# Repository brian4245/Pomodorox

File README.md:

# Pomodorox
Pomodorox is a project that helps to the high school´s students for studying without distractions

On shape: https://cad.onshape.com/documents/2d539401d5eeff7b5a051a5e/w/acb2298a33fe291c39ed5225/e/8e80be298c9f318b740c5d51?renderMode=0&uiState=6a6d26c64163ef4042c04433

# Motivation
Well, I did this project because I realized that many people try to study but many times they don´t study, and it is because we use a laptop or a smarthphone to use a technique for study, but many times these technology products give us many distractions, and the better option to use could be an analogyc product that you can use to study.

# Instructions to build it
After all I know you the functions that I used for the circuit, I used the default functions like setup and loop. In adittion I use these functions:
void ultrasonico(); this function is to start the work of ultrasonic distance sensor, it starts when you press the red button in the IR remote, and it detects if you are near or far, and if you near the circuit start to works as a pomodoro.
``` C++
void reset(); //This one is to reset the values of time at the pomodoro (twenty five minutes).
void reloj(); //This another one is to start the clock pomodoro for study time.
void descanso(); //This one is to start the break (five minutes).
void start(); //This one is to start the words that going to give you a gretting.
void plazos(); // With this one you can decides if you wanna continue with the break or with the focus time.
```

Well, first you need to configure you ultrasonic distance sensor for detects the distance in a well way. I this step I use this code to configure it: 
``` C++
void ultrasonico(){ 
  digitalWrite(trigpin, LOW);  
  delayMicroseconds(2);
  digitalWrite(trigpin, HIGH);
  delayMicroseconds(10); 
  digitalWrite(trigpin, LOW);
  
  duration = pulseIn(echopin, HIGH);
  distance = duration / 58.2;
  Serial.println(distance);
}
```
I use a function to become the code more versatil. Oh, before it you need to place the pins at setup, like this:
```C++
pinMode(trigpin, OUTPUT);
pinMode(echopin, INPUT);
```
Variables:
```C++
int trigpin = 4;
int echopin = 5;
```
Well after it, now you need to configure the IR remote and the IR sensor to POMODORO going to able to detect you position in yout desktop and If you really study. For it, I use this variable:
```C++
int IRD = 3;
```
Then I placed it at setup to begin the IR sensor:
```C++
  IrReceiver.begin(IRD);
```
Well, after it the third step is to configure the button that you use to start the system of POMODORO, I placed the code in loop:
```C++
 int IRcode = 0; 
  if(IrReceiver.decode()){
    IRcode = IrReceiver.decodedIRData.command; 
    Serial.println(IRcode);
    IrReceiver.resume();
  }
```
Well I declared " int IRcode = 0 " to avoid some mistkae with the control at the moment I don´t need it more, and I place the conditional to start the IR sensor for the code, IRcode is the Data number that the IRremote give us, Then I print it in monitor serial, after it I reset the IRcode, to start all again.
```C++
 if (IRcode == 162){
    startcontrol = true; <= this function is to start the greeting at the display
    ultrasonicocontrol = true; <= this one is to start the ultrasonic distance to POMODORO can see if you are near (1m).
    yasepuede = true; <= this one is for the POMODORO can understand that you are ready.
  }
```
Well, after it you need to configure the code for the chronometer, this step is very crucial because you need it to do working the POMODORO

Well, this code I used for the chronometer in the focus time.
```C++
void reloj(){
  lcd.setCursor(0, 0);
  lcd.print("POMODORO");
  lcd.setCursor(0, 1);
  
  if (MINUTOS < 10) lcd.print("0"); 
  lcd.print(MINUTOS);
  lcd.print(":");
  if (SEGUNDOS < 10) lcd.print("0"); 
  lcd.print(SEGUNDOS);
  
  cronometrofocus = true;
}
```
 Within that code I placed the boolean variable "cronometrofocus" it is in charge to do works the chronometer in reality.
```C++
  // 5. CRONÓMETROS 
  if (cronometrofocus == true){
    if (millis() - tiempoinicio >= 1000){
      tiempoinicio = millis();
      SEGUNDOS++;
      if (SEGUNDOS == 60){
        SEGUNDOS = 0;
        MINUTOS++;
      }
    }
  }
  
  if (cronometrodespeje == true){
    if (millis() - tiempoiniciodescanso >= 1000){
      tiempoiniciodescanso = millis();
      SEGUNDOSD++;
      if (SEGUNDOSD == 60){
        SEGUNDOSD = 0;
        MINUTOSD++;
      }
    }
  }
```
Well at that code chronometer that I use, because they have a similar system to work the only thing that changes is the variables.
Well and the function for the break works in a similar way like the function for the focus time.
```C++
void descanso(){
  lcd.setCursor(9, 0);
  lcd.print("DESCANSO");
  lcd.setCursor(9, 1);
  if (MINUTOSD < 10) lcd.print("0"); 
  lcd.print(MINUTOSD);
  lcd.print(":");
  if (SEGUNDOSD < 10) lcd.print("0"); 
  lcd.print(SEGUNDOSD);
  
  cronometrodespeje = true;
}

```
The only thing that change is the place where the message is locate.

Well, the another function works when you press the red button:
```C++
void start(){
  yasepuede = true;
  ultrasonico(); // Ejecutamos la lectura real del sensor antes de evaluar
  if (distance <= 100 && distance > 0){ 
    digitalWrite(bocina, HIGH);
    lcd.setCursor(0,0);
    lcd.print("EMPEZEMOS");
    delay(1000);
    lcd.clear();
    lcd.print("LET'S MOVE ON");
    delay(1000);
    lcd.clear();
    digitalWrite(bocina, LOW);
  }
}
```
I placed the boolean variable to controle the if the clock is able to works or maybe no.

Then in the same place I placed the control for the distance, it controls if you are near or far to the POMODORO. Well I named the LED as "bocina". because at first I was thinking use an Piezo, but after thinking well I realized that is better use a LED, because it is less anoying. 

Well, I use some boolean variables to control the functions in a better way:
```C++
  if (startcontrol == true){
    start();
    startcontrol = false;
  }
  
  if (RELOJ == true){
    reloj();
  } 

  if (descansocontrol == true){
    descanso();
  }
```
I placed it at loop.

Well, I used this code to control the buttons, it was more useful because it avoid that the code confuse with another delay, because at first I used delay, but it didn´t work in a well way, so is better to use millis to control a multitasking.
```C++
  ActualFocus = digitalRead(focus);
  if (ActualFocus == HIGH && AnteriorFocus == LOW && yasepuede == true) {
    reset(); // Reseteamos los tiempos justo al empezar el tramo
    RELOJ = true;
    descansocontrol = false;
    cronometrodespeje = false;
    delay(50); // Pa que no se repita
  }
  AnteriorFocus = ActualFocus;

  ActualDespeje = digitalRead(despeje);
  if (ActualDespeje == HIGH && AnteriorDespeje == LOW && yasepuede == true) {
    reset(); 
    controlplazos = false;
    descansocontrol = true;
    RELOJ = false;
    cronometrofocus = false;
    delay(50); // Pa que no se repita
  }
  AnteriorDespeje = ActualDespeje;
```

### ¿How I use it?
It´s very easy to use, the only thing that you do is press the red button in the IR remote control when you are near (1m) to pomodorox. After it, the scren give you some instructions to continue the pomodoro (the button green is for continue studying and the other button green is for the break).
## Materials ##
- 1 Arduino uno
- 1 resistor
- 1 led
- 2 push buttons 
- 1 Ultrasonic distance sensor
-  1 IR sensor
-  1 IR remote

## Schematic ##

## BOM ##
| ITEM | Purpose | Price | Source |
| :---: | :---: | :---: | :---: |
| Ultrasonic Distance Sensor | Detect the distance where you are, and it decides if you are ready to study | S/ 8|  Nanoparuro |
| LED(red) | It is a signal to know if the Ultrasonic sensor is on | S/ 1.00 | Nanoparuro |
| Arduino UNO | It is to control the circuit | S/ 30.00 | Nanoparuro  |
| I2C LCD | It is to use with fewer pins | S/ 7.00 | Nanoparuro  |
| LCD 20x4 | It is crucial to represent the chronometer POMODORO | S/ 22.00 | Electromanía  |
| IR remote | It is for controlling the start of the pomodoro | S/ 10.00 | Nanoparuro |
| IR sensor | It is to detect the IR remote | S/ 10.00 | Nanoparuro  |
| 2 Push Buttons | To activate the POMODORO clock | S/ 1.40 | electromanía |
| PCB | To conncect all of the componentes in the circuit | S/ 120 | VILLACONTROL |

## Magazine ##

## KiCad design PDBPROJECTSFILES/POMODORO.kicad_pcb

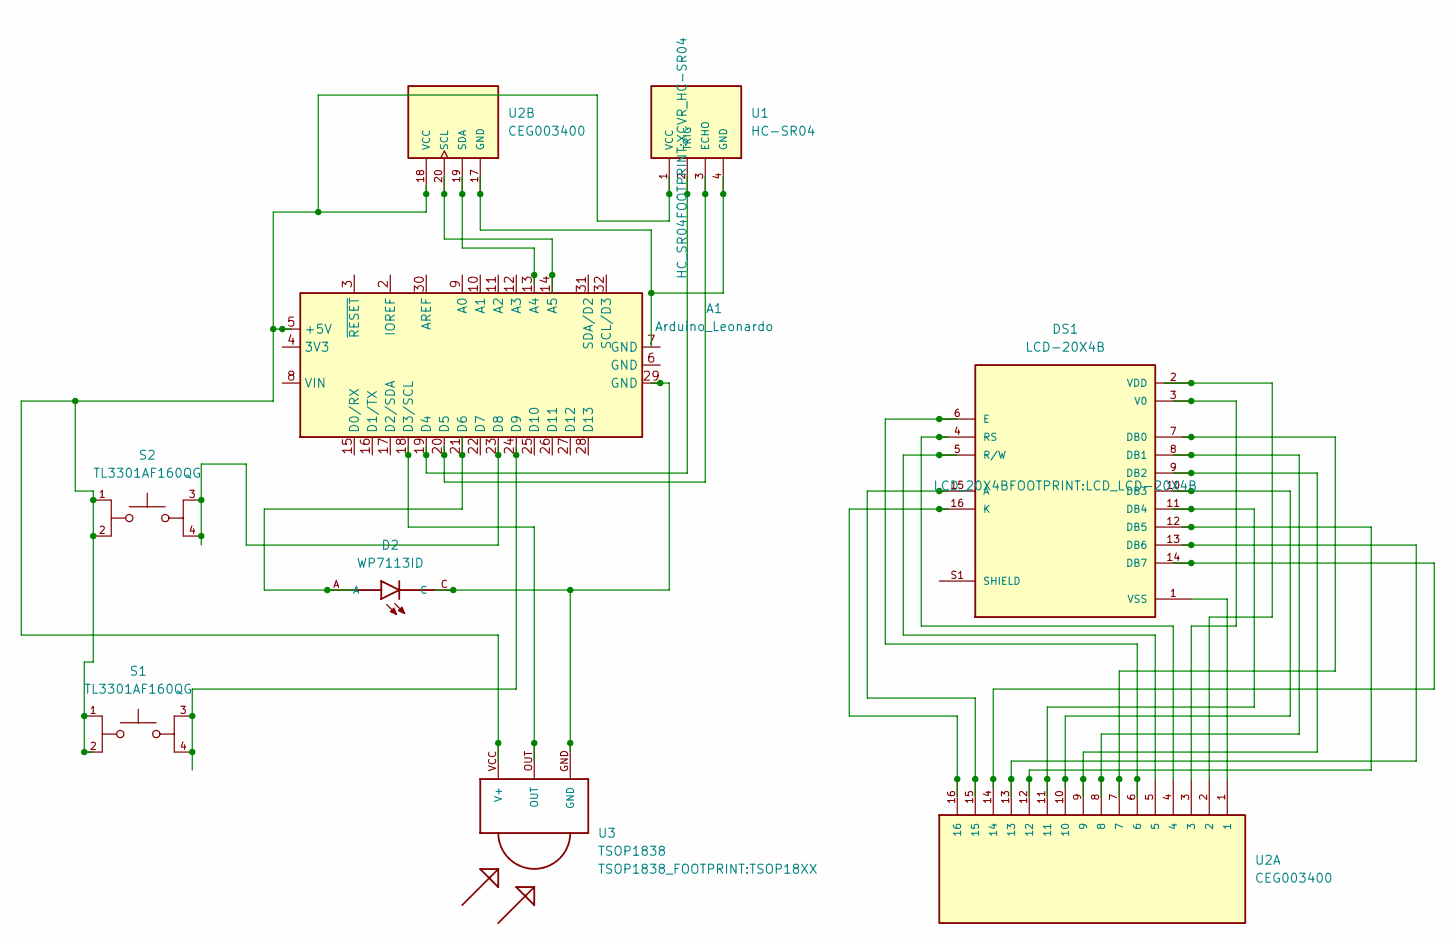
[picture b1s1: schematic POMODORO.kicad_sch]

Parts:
A1: Arduino_Leonardo; Arduino_UNO_R3
D2: WP7113ID; LED_WP7113ID
DS1: LCD-20X4B; LCD_LCD-20X4B; PARTREV N/A
S1, S2: TL3301AF160QG; SW_TL3301AF160QG; PARTREV E
U1: HC-SR04; XCVR_HC-SR04
U2: CEG003400; MODULE_CEG003400; PARTREV N/A
U3: TSOP1838; TSOP18XX

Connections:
unnamed: A1.5 (+5V), S1.1, S1.2, S2.1, S2.2, U1.1 (VCC), U2.18 (VCC), U3.VCC (V+)
unnamed: A1.13 (A4), U2.19 (SDA)
unnamed: A1.14 (A5), U2.20 (SCL)
unnamed: A1.18 (D3/SCL), U3.OUT
unnamed: A1.19 (D4), U1.2 (TRIG)
unnamed: A1.20 (D5), U1.3 (ECHO)
unnamed: A1.21 (D6), D2.A
unnamed: A1.23 (D8), S2.3, S2.4
unnamed: A1.24 (D9), S1.3, S1.4
unnamed: A1.29 (GND), D2.C, U3.GND
unnamed: DS1.15 (A), U2.15
unnamed: DS1.7 (DB0), U2.7
unnamed: DS1.8 (DB1), U2.8
unnamed: DS1.9 (DB2), U2.9
unnamed: DS1.10 (DB3), U2.10
unnamed: DS1.11 (DB4), U2.11
unnamed: DS1.12 (DB5), U2.12
unnamed: DS1.13 (DB6), U2.13
unnamed: DS1.14 (DB7), U2.14
unnamed: DS1.6 (E), U2.6
unnamed: DS1.16 (K), U2.16
unnamed: DS1.4 (RS), U2.4
unnamed: DS1.5 (R/W), U2.5
unnamed: DS1.S1 (SHIELD), DS1.S2 (SHIELD), DS1.S3 (SHIELD), DS1.S4 (SHIELD)
unnamed: DS1.3 (V0), U2.3
unnamed: DS1.2 (VDD), U2.2
unnamed: DS1.1 (VSS), U2.1
unnamed: U1.4 (GND), U2.17 (GND)

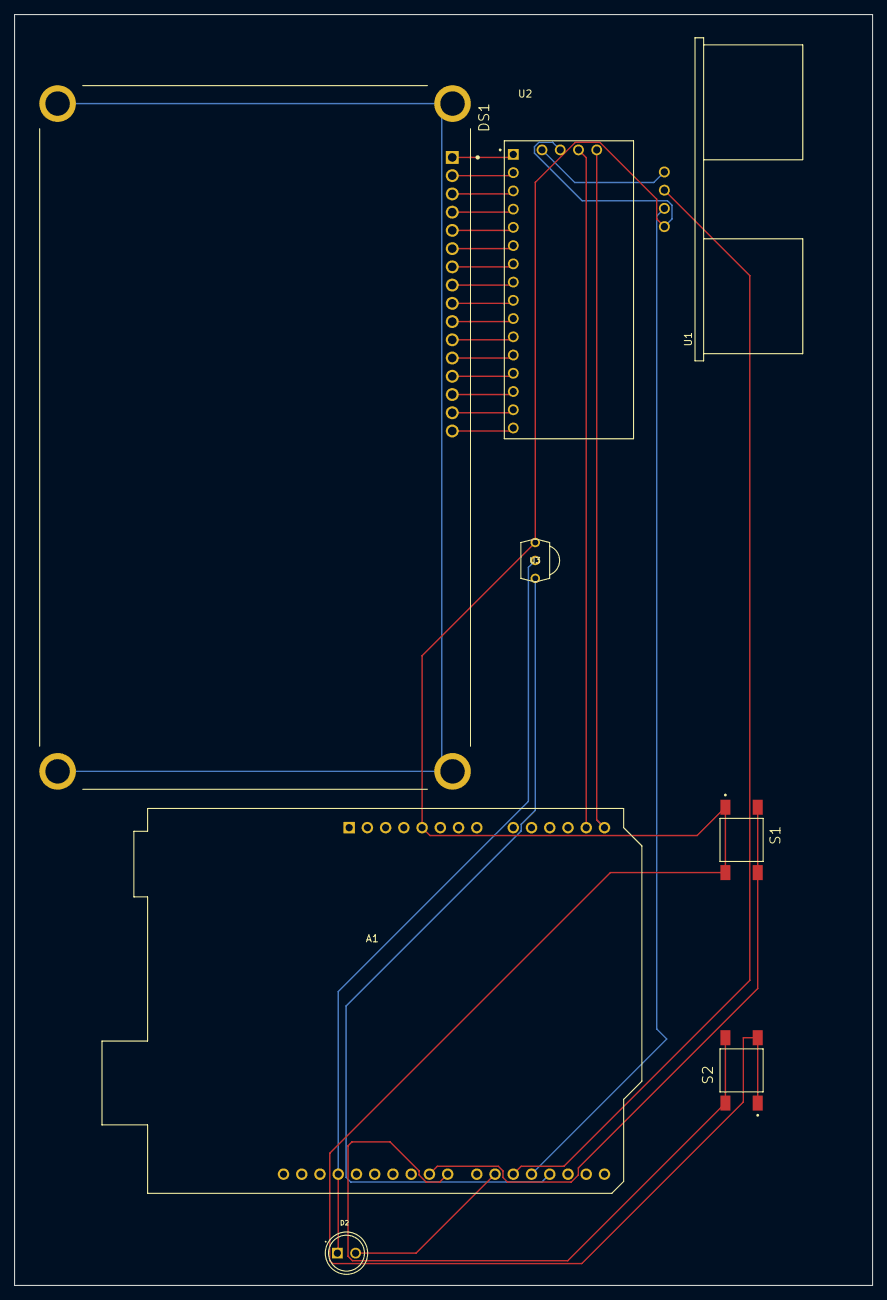
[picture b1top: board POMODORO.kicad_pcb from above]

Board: 2 copper layers, 119.5 x 177.0 mm, 8 parts (0 on the bottom side), 28 nets.

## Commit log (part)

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2026-05-04 Initialize README with project details and instructions
    Added project overview, usage instructions, materials list, and schematic section.
2026-05-04 Add schematic image to README
2026-05-05 Correct image formatting in README
    Fix image syntax in README.md
2026-05-05 Change example image in README
    Updated image link in README to a new source.
2026-05-17 SCHEMATICKICAD
2026-06-08 Rename project from Nall-e to Pomodorox
    Updated project name and removed unnecessary components.
2026-06-09 Change the code
2026-06-09 Changed the readme
2026-06-09 Rename Captura de pantalla 2026-06-09 122925.png to SCHEMATICCIRCUIT.png
2026-06-10 Rename Captura de pantalla 2026-06-09 195620.png to 3dDesign.png
2026-06-13 Add magazine image to README
2026-06-13 Changing distance control
2026-06-15 Update usage instructions in README.md
    Clarified usage instructions and fixed typos in README.
2026-06-15 Add motivation section to README
    Added a motivation section explaining the purpose of the project and how it helps students study without distractions.
2026-06-16 Expand README with build instructions and usage
    Added detailed instructions for building and using the Pomodorox project, including function descriptions and setup steps.
2026-06-16 Fix code formatting in README for ultrasonic sensor
    Corrected the formatting of the code snippet for clarity.
2026-06-16 Fix grammar in ultrasonic sensor configuration section
    Corrected grammar and formatting in README.
2026-06-16 Enhance README with clearer ultrasonic sensor setup
    Updated README to improve clarity and formatting of the ultrasonic distance sensor configuration section.
2026-06-16 Improve README with formatted code and clearer function descriptions
    Updated function descriptions and code formatting in README.
2026-06-16 Update README with setup instructions and variable details
    Corrected formatting and clarified instructions for setup and variable declarations.
2026-06-16 Fix typos and enhance README instructions
    Corrected typos and improved clarity in the README.
2026-06-16 Enhance README with code explanations and usage
    Updated README with detailed explanations of the code functionality and usage instructions.
2026-06-16 ORGANIZE THE REPOSITORY
2026-06-17 ADD KICAD FILES
2026-06-17 organize the files
2026-06-17 FILESPCBPROJECT
2026-06-17 PCDFILESTOTAL
2026-06-17 ADD THE LINK
2026-06-17 Trying to place the BOM
2026-06-17 Improve BOM table formatting in README.md
    Updated the BOM table format for better readability.
2026-06-17 Update BOM table to include source information
    Added a 'Source' column to the BOM table for clarity.
2026-06-24 Become the code cohesive
